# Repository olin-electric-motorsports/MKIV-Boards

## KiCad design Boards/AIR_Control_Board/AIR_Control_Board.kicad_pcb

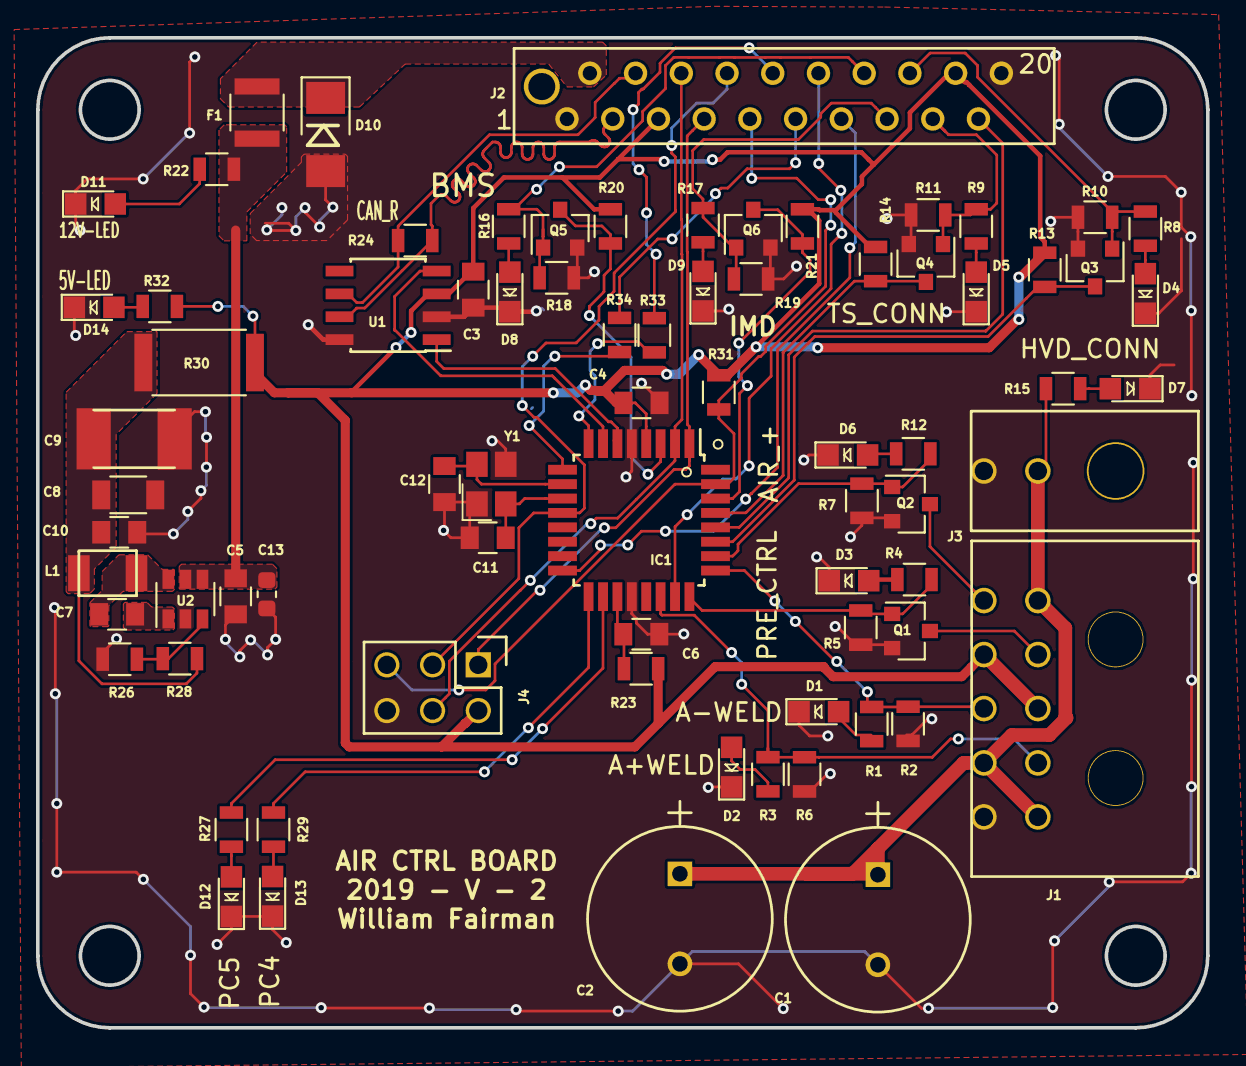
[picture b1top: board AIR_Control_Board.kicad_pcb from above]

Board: 2 copper layers, 65.0 x 55.0 mm, 76 parts (0 on the bottom side), 56 nets.

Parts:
C1, C2: CP_1mF; C_Radial_D10_L13_P5_OEM
C3, C4, C5, C7: C_0.1uF; C_0805_OEM
C6: C_100pF; C_0805_OEM
C8: C_22uF; C_1206_OEM
C9: C_33uF; C_1812_updated
C10: C_47uF; C_0805_OEM
C11, C12: C_30pF; C_0805_OEM
C13: C_2.2uF; C_0603_1608Metric
D1, D2, D3, D4, D5, D6, D7, D8, D9, D11, D12, D13, D14: LED_0805; LED_0805_OEM
D10: D_Zener_18V; DO-214AA
F1: 500mA; Fuse_1210
IC1: ATMEGA16M1; TQFP-32_7x7mm_Pitch0.8mm
J1: MicroFit_RA_10
J2: MM_F_VT_20; micromatch_female_vert_20
J3: MicroFit_RA_V_2
J4: CONN_02X03; Pin_Header_Straight_2x03
L1: L_100uH
Q1, Q2, Q3, Q4, Q5, Q6: SSM3K333R; SOT-23F
R1, R3, R4, R12, R24, R27, R29, R32, R33, R34: R_200; R_0805_OEM
R2, R5, R6, R7, R13, R14, R20, R21, R31: R_10K; R_0805_OEM
R8, R9, R15, R16, R17, R22: R_1K; R_0805_OEM
R10, R11, R18, R19, R28: R_100K; R_0805_OEM
R23: R_100; R_0805_OEM
R26: R_25K; R_0805_OEM
R30: R_0_2512; R_2512_OEM
U1: MCP2561-E_SN; SOIC-8_3.9x4.9mm_Pitch1.27mm_OEM
U2: TPS560430YF; SOT-23-6_OEM
Y1: Crystal_SMD; Crystal_SMD_FA238

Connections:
+12V: D10.1, F1.1, J2.2
/AIR+LSD: IC1.26, Q2.1, R7.1, R12.1
/AIR+_Weld_Detect: IC1.22, J1.4, R3.1, R6.1
/AIR-_Weld_Detect: IC1.25, J1.8, R1.1, R2.1
/Air+12V: C1.1, C2.1, J1.1, J1.5, J1.9, J3.1, R15.1
/Air+GND: J1.6, Q2.3
/BMS_Sense: IC1.16, J2.13
/CAN_N: J2.4, R24.2, U1.6
/CAN_P: J2.3, R24.1, U1.7
/Cooling_Pressure_Sense: IC1.28, J2.19
/IMD_Sense: IC1.23, J2.12
/MISO: IC1.1, J2.7, J4.1
/MOSI: IC1.2, J2.6, J4.4
/P_LED_1: IC1.17, R29.1
/P_LED_2: IC1.18, R27.1
/Precharge-: J1.2, Q1.3
/PrechargeCTL: IC1.24, Q1.1, R4.1, R5.1
/RESET: IC1.31, J2.9, J4.5, R31.2
/RJ45_LED1: IC1.8, R33.1
/RJ45_LED2: IC1.9, R34.1
/SCK: IC1.12, J2.8, J4.3
/SenseConnToHVD: IC1.27, Q3.3, R13.2
/SenseMainTSConn: IC1.29, Q4.3, R14.2
/ShutdownSense_BMS: J2.14, Q5.1, R16.1, R18.1
/ShutdownSense_HVD_Conn: J2.16, Q3.1, R8.1, R10.1
/ShutdownSense_IMD: J2.15, Q6.1, R17.1, R19.1
/ShutdownSense_MainPack: J2.17, Q4.1, R9.1, R11.1
/XCAN_N: IC1.7, U1.4
/XCAN_P: IC1.6, U1.1
/ss_BMS: IC1.3, Q5.3, R20.2
/ss_IMD: IC1.30, Q6.3, R21.2
GND: C1.2, C2.2, C3.2, C4.2, C5.2, C6.2, C8.2, C9.2, C10.2, C11.2, C12.2, C13.2, D1.1, D2.1, D3.1, D4.1, D5.1, D6.1, D7.1, D8.1, D9.1, D10.2, D11.1, D12.1, D13.1, D14.1, IC1.5, IC1.20, J1.10, J2.1, J2.20, J3.2, J4.6, Q1.2, Q2.2, Q3.2, Q4.2, Q5.2, Q6.2, R2.2, R5.2, R6.2, R7.2, R10.2, R11.2, R18.2, R19.2, R26.2, U1.2, U1.8, U2.2, Y1.2, Y1.4
unnamed: C6.1, IC1.19, R23.2
unnamed: C7.1, U2.1
unnamed: C7.2, L1.1, U2.6
unnamed: C8.1, C9.1, C10.1, L1.2, R28.1, R30.2
unnamed: C11.1, IC1.11, Y1.1
unnamed: C12.1, IC1.10, Y1.3
unnamed: C5.1, C13.1, F1.2, R22.1, U2.4, U2.5
unnamed: D1.2, R1.2
unnamed: D2.2, R3.2
unnamed: D3.2, R4.2
unnamed: D4.2, R8.2
unnamed: D5.2, R9.2
unnamed: D6.2, R12.2
unnamed: D7.2, R15.2
unnamed: D8.2, R16.2
unnamed: D9.2, R17.2
unnamed: D11.2, R22.2
unnamed: D12.2, R27.2
unnamed: D13.2, R29.2
unnamed: D14.2, R32.2
unnamed: J2.10, R33.2
unnamed: J2.11, R34.2
unnamed: R26.1, R28.2, U2.3
VCC: C3.1, C4.1, IC1.4, J1.3, J1.7, J2.5, J2.18, J4.2, R13.1, R14.1, R20.1, R21.1, R23.1, R30.1, R31.1, R32.1, U1.3

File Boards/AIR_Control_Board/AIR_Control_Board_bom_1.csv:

Component,Description,Part,References,Value,Footprint,Quantity Per PCB,Datasheet,Package,MPN,Purchasing Link,MFN,PurchasingLink,DK,Purchase_Link
1,,CP_1mF,C1 C2,CP_1mF,C_Radial_D10_L13_P5_OEM,2,http://nichicon-us.com/english/products/pdfs/e-uvz.pdf,"Radial, Can",493-1305-ND,https://www.digikey.com/products/en?keywords=493-1305-ND,Digi-Key,,,
2,"Capacitor, 0.1uF, 50V, 5%, 0805",C_0.1uF,C3 C4 C7 C10,C_0.1uF,C_0805_OEM,4,http://datasheets.avx.com/X7RDielectric.pdf,Value,478-3352-1-ND,,Digi-Key,https://www.digikey.com/products/en?keywords=478-3352-1-ND,,
3,"Capacitor, 100pF, 50V, 5%, 0805",C_100pF,C6,C_100pF,C_0805_OEM,1,https://content.kemet.com/datasheets/KEM_C1003_C0G_SMD.pdf,Value,399-1122-1-ND,,Digi-Key,https://www.digikey.com/product-detail/en/kemet/C0805C101J5G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,,
4,CAP CER 1UF 25V X7R 0805,C_1uF,C9,C_1uF,C_0805_OEM,1,http://datasheets.avx.com/X7RDielectric.pdf,Value,478-10487-1-ND,,Digi-Key,https://www.digikey.com/product-detail/en/avx-corporation/08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,,
5,"Capacitor, 22uF, 16V, 20%, 1206",C_22uF,C5,C_22uF,C_1206_OEM,1,http://www.samsungsem.com/kr/support/product-search/mlcc/__i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,Value,1276-2725-1-ND,,Digi-Key,https://www.digikey.com/products/en?keywords=1276-2725-1-ND,,
6,"Capacitor, 30pF, 50V, 5%, 0805",C_30pF,C11 C12,C_30pF,C_0805_OEM,2,https://media.digikey.com/pdf/Data%20Sheets/Samsung%20PDFs/C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,Value,1276-1130-1-ND,,Digi-Key,https://www.digikey.com/product-detail/en/samsung-electro-me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,,
7,"Capacitor, 47uF, 6.3V, 20%, 0805",C_47uF,C8,C_47uF,C_0805_OEM,1,http://www.yuden.co.jp/productdata/catalog/en/mlcc_all_e.pdf,Value,587-4280-1-ND,,Digi-Key,https://www.digikey.com/product-detail/en/taiyo-yuden/JMK212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,,
8,"Diode, Zener, 18V, 5W, 5%",D_Zener_18V,D10,D_Zener_18V,DO-214AA,1,http://www.mccsemi.com/up_pdf/SMBJ5338B-SMBJ5388B(SMB).pdf,DO-214AA (SMB),SMBJ5355B-TPMSCT-ND,,Digi-Key,https://www.digikey.com/products/en?keywords=SMBJ5355B-TPMSCT-ND,,
9,"LED, Green, 2.2V, 20mA, 0805",LED_0805,D1 D2 D3 D4 D5 D6 D7 D8 D9 D11 D12 D13 D14,LED_0805,LED_0805_OEM,13,http://www.osram-os.com/Graphics/XPic9/00078860_0.pdf,Value,475-1410-1-ND,,DK Digi-Key,https://www.digikey.com/products/en?keywords=475-1410-1-ND,,
10,"Fuse, PTC, 500mA, 16V, 1210",F_500mA_16V,F1,500mA,Fuse_1210,1,https://belfuse.com/resources/CircuitProtection/datasheets/0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,Value,507-1786-1-ND,,Digi-Key,https://www.digikey.com/product-detail/en/bel-fuse-inc/0ZCH0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,,
11,"Microcontroller, 8-bit, 1KB RAM, 16KB Flash",ATMEGA16M1,IC1,ATMEGA16M1,TQFP-32_7x7mm_Pitch0.8mm,1,http://www.atmel.com/Images/Atmel-8209-8-bit%20AVR%20ATmega1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,Value,ATMEGA16M1-AU-ND,,Digi-Key,https://www.digikey.com/product-detail/en/atmel/ATMEGA16M1-A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,,
12,"Connector header through hole 2x3 0.100"" (2.54mm)",CONN_02X03,J4,CONN_02X03,Pin_Header_Straight_2x03,1,http://portal.fciconnect.com/Comergent//fci/drawing/67996.pdf,Value,609-3234-ND,,Digi-Key,https://www.digikey.com/product-detail/en/amphenol-fci/67997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,,
13,Micro-MaTch connector 20 pin female vertical,MM_F_VT_20,J2,MM_F_VT_20,micromatch_female_vert_20,1,http://www.te.com/commerce/DocumentDelivery/DDEController?Ac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,,2-338068-0,,TE,http://www.te.com/global-en/product-2-338068-0.html,,
14,,MicroFit_RA_10,J1,MicroFit_RA_10,MicroFit_RA_10,1,https://www.molex.com/pdm_docs/sd/430451000_sd.pdf,,WM1817-ND,,DK,https://www.digikey.com/product-detail/en/molex/0430451000/W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,,
15,,MicroFit_RA_V_2,J3,MicroFit_RA_V_2,MicroFit_RA_V_2,1,https://www.molex.com/pdm_docs/sd/430450200_sd.pdf,,WM1865-ND,https://www.digikey.com/product-detail/en/molex/0430450200/W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,,,MFN,
16,"Inductor, 4.7uH, 4.4A, 25mOhm, 20%",L_4.7uH,L1,L_4.7uH,4.7uH_Inductor_OEM,1,https://product.tdk.com/info/en/documents/wdcatalog/withdraw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,Value,445-6583-1-ND,,Digi-Key,https://www.digikey.com/product-detail/en/tdk-corporation/VL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,,
17,"MOSFET, N-channel, 30V, 6A",SSM3K333R,Q1 Q2 Q3 Q4 Q5 Q6,SSM3K333R,SOT-23F,6,https://drive.google.com/drive/folders/0B-V-iZf33Y4GNzhDQTJZanJRbVk,SOT-23-3 Flat Leads,SSM3K333RLFCT-ND,,Digi-Key,https://www.digikey.com/product-detail/en/toshiba-semiconduc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,,https://www.digikey.com/product-detail/en/toshiba-semiconduc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
18,"Resistor, 0 ohm jumper, 3W, 2512",R_0_2512,R30,R_0_2512,R_2512_OEM,1,http://www.te.com/commerce/DocumentDelivery/DDEController?Ac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,,A121322CT-ND,,DK,https://www.digikey.com/products/en?keywords=A121322CT-ND,,
19,"Resistor, 100, 0.25W, 1%, 0805",R_100,R23,R_100,R_0805_OEM,1,https://www.seielect.com/Catalog/SEI-rncp.pdf,Value,RNCP0805FTD100RCT-ND,,Digi-Key,https://www.digikey.com/products/en?keywords=RNCP0805FTD100RCT-ND,,
20,"Resistor, 100K, 0.125W, 1%, 0805",R_100K,R10 R11 R18 R19,R_100K,R_0805_OEM,4,https://industrial.panasonic.com/cdbs/www-data/pdf/RDA0000/A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,,P100KCCT-ND,,DK,https://www.digikey.com/product-detail/en/panasonic-electron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,,
21,"Resistor, 10K, 0.25W, 1%, 0805",R_10K,R2 R5 R6 R13 R14 R20 R21 R25 R26 R31,R_10K,R_0805_OEM,10,http://www.bourns.com/data/global/pdfs/CRS.pdf,,CRS0805-FX-1002ELFCT-ND,,DK,https://www.digikey.com/products/en?keywords=CRS0805-FX-1002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,,
22,"Resistor, 100K, 0.125W, 1%, 0805",R_100K,R7,R_10K,R_0805_OEM,1,https://industrial.panasonic.com/cdbs/www-data/pdf/RDA0000/A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,,P100KCCT-ND,,DK,https://www.digikey.com/product-detail/en/panasonic-electron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,,
23,"Resistor, 1K, 0.25W, 1%, 0805",R_1K,R8 R9 R15 R16 R17 R22,R_1K,R_0805_OEM,6,https://www.seielect.com/Catalog/SEI-rncp.pdf,,RNCP0805FTD1K00CT-ND,,DK,https://www.digikey.com/products/en?keywords=RNCP0805FTD1K00CT-ND,,
24,"Resistor, 200, 0.125W, 5%, 0805",R_200,R1 R3 R4 R24 R27 R29 R32 R33 R34,R_200,R_0805_OEM,9,https://www.seielect.com/Catalog/SEI-RMCF_RMCP.pdf,Value,RMCF0805JT200RCT-ND,,DK Digi-Key,https://www.digikey.com/products/en?keywords=RMCF0805JT200RCT-ND,,
25,"Resistor, 1K, 0.25W, 1%, 0805",R_1K,R12,R_200,R_0805_OEM,1,https://www.seielect.com/Catalog/SEI-rncp.pdf,,RNCP0805FTD1K00CT-ND,,DK,https://www.digikey.com/products/en?keywords=RNCP0805FTD1K00CT-ND,,
26,"Resistor, 51.1K, 0.125W, 1%, 0805",R_51.1K,R28,R_51.1K,R_0805_OEM,1,https://industrial.panasonic.com/cdbs/www-data/pdf/RDA0000/A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,,P51.1KCCT-ND,,DK,https://www.digikey.com/product-detail/en/panasonic-electron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,,
27,"High speed CAN transceiver, 1Mb/s",MCP2561-E_SN,U1,MCP2561-E_SN,SOIC-8_3.9x4.9mm_Pitch1.27mm_OEM,1,http://www.microchip.com/mymicrochip/filehandler.aspx?ddocna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,,MCP2561-E/SN-ND,,DK,https://www.digikey.com/products/en?keywords=mcp2561-e%2Fsn,,
28,"Buck converter, 4.5-17V input, adj 0.76-7V output, 1A, 580kHz",TPS561201,U2,TPS561201,SOT-23-6_OEM,1,http://www.ti.com/lit/ds/symlink/tps561201.pdf,Value,TPS561201,,Digi-Key,https://www.digikey.com/products/en?keywords=296-46928-1-ND,,
29,CRYSTAL 16.0000MHZ 18PF SMD,Crystal_SMD,Y1,Crystal_SMD,Crystal_SMD_FA238,1,https://support.epson.biz/td/api/doc_check.php?dl=brief_FA-2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,Value,SER3686CT-ND,,Digi-Key,https://www.digikey.com/products/en?keywords=SER3686CT-ND,,





Component Groups:,29
Component Count:,76
Fitted Components:,76
Number of PCBs:,1
Total components:,76
Schematic Version:,1
Schematic Date:,2018-11-01
BoM Date:,Sun 10 Feb 2019 09:32:41 AM EST
Schematic Source:,/home/william/Desktop/MKIV-Boards/Boards/AIR_Control_Board/AIR_Control_Board.sch
KiCad Version:,Eeschema 5.0.0-fee4fd1~66~ubuntu16.04.1

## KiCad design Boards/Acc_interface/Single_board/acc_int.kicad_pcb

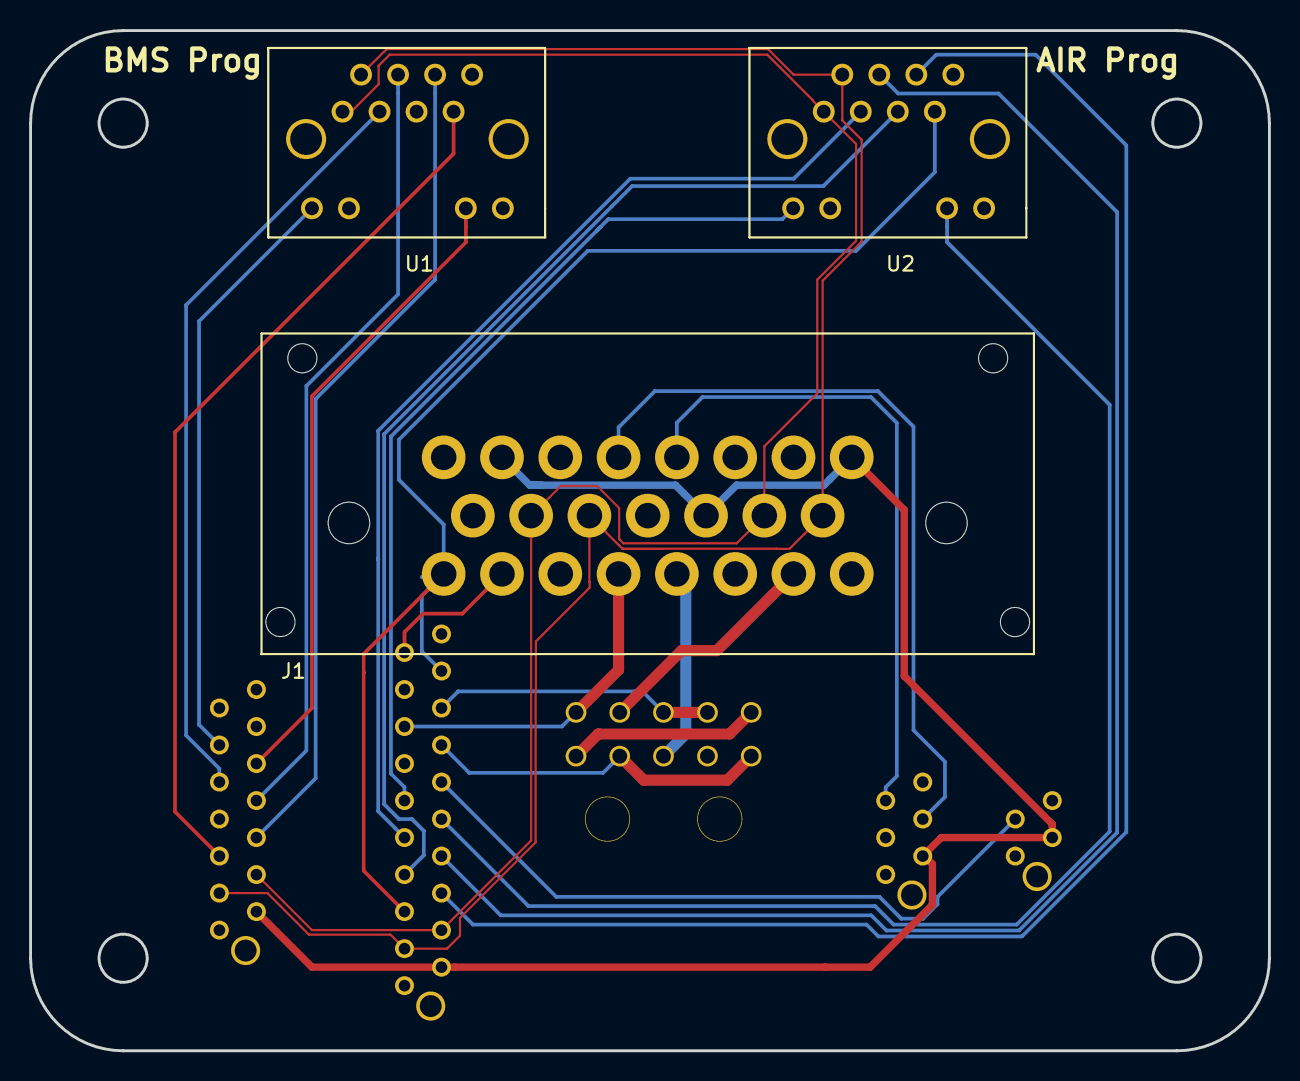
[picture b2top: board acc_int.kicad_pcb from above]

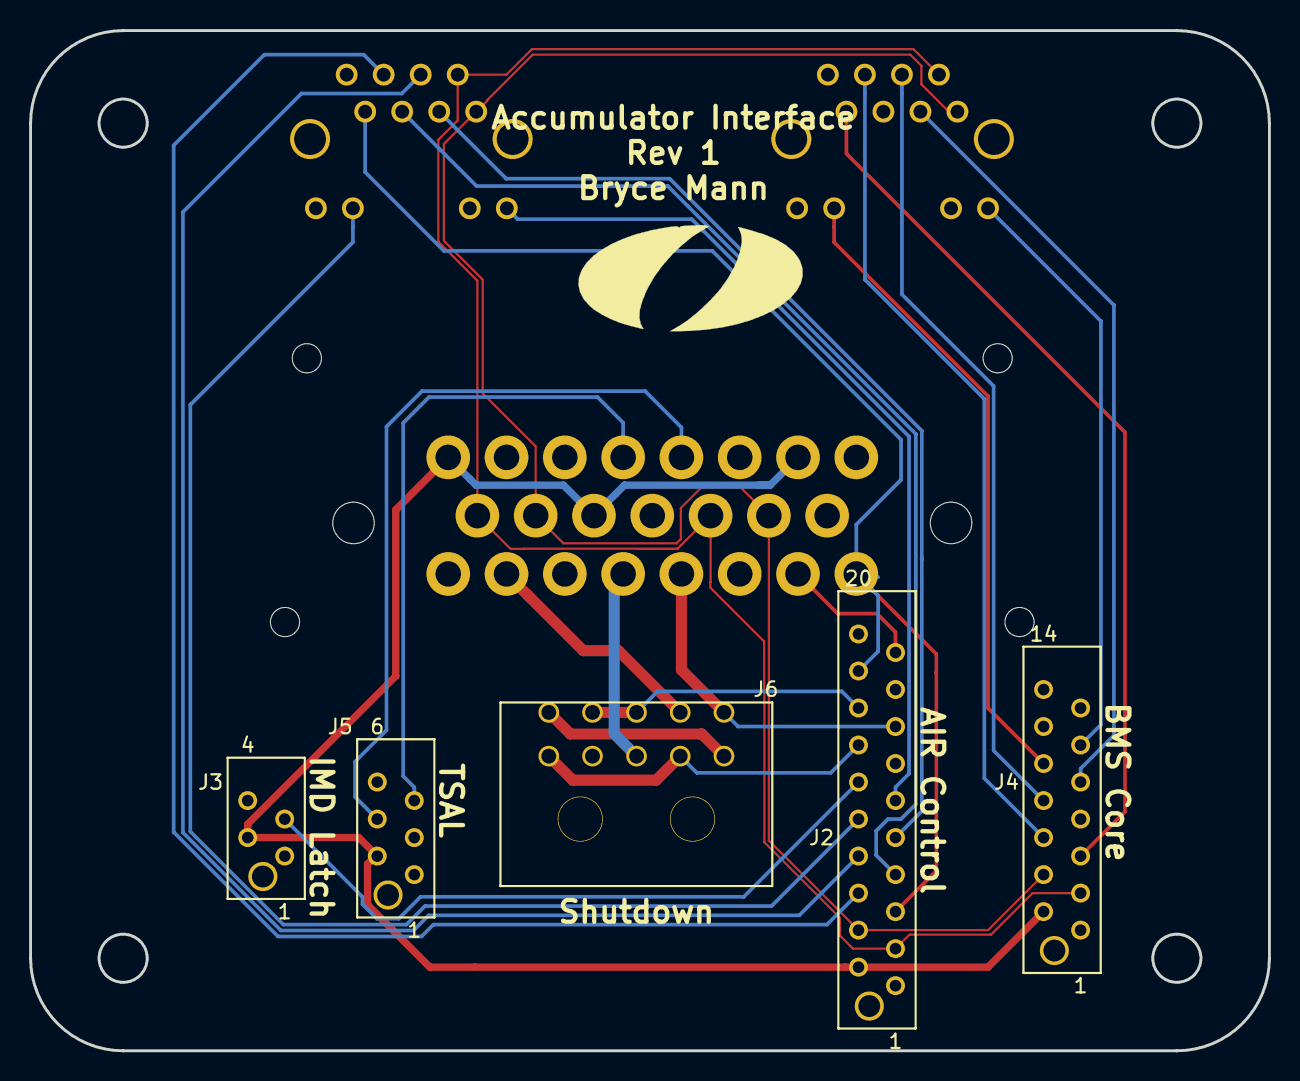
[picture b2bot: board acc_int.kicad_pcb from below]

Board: 4 copper layers, 85.0 x 70.0 mm, 8 parts (5 on the bottom side), 33 nets.

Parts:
J1: Ampseal_23_VT; Ampseal_23
J2: MM_F_RA_20; micromatch_female_vert_20
J3: MM_F_RA_04; micromatch_female_vert_4
J4: MM_F_RA_14; micromatch_female_vert_14
J5: MM_F_RA_06; micromatch_female_vert_6
J6: MicroFit_RA_10
U1, U2: RJ45_VT; RJ45-Vertical

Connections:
/5V_AIR: J1.16, J2.5, J2.18, U2.7
/5V_BMS: J4.5, U1.7
/12V: J1.2, J1.8, J1.13, J2.2, J3.2, J4.2, J5.2
/BMS_SENSE: J2.13, J4.13
/BSPD_Current_sense: J1.23, J4.14
/CAN_HIGH: J1.11, J1.15, J2.3, J4.3, U1.2, U2.2
/CAN_LOW: J1.10, J1.14, J2.4, J4.4, U1.1, U2.1
/Cooling_pressure_sense: J1.17, J2.19
/FAN_PWM: J1.21, J4.12
/IMD_SENSE: J2.12, J3.3
/LED1_AIR: J2.10, U2.10
/LED1_BMS: J4.10, U1.10
/LED2_AIR: J2.11, U2.12
/LED2_BMS: J4.11, U1.12
/MISO_AIR: J2.7, U2.5
/MISO_BMS: J4.7, U1.5
/MOSI_AIR: J2.6, U2.6
/MOSI_BMS: J4.6, U1.6
/RESET_AIR: J2.9, U2.3
/RESET_BMS: J4.9, U1.3
/SCK_AIR: J2.8, U2.4
/SCK_BMS: J4.8, U1.4
/Shutdown_BMS: J2.14, J6.2, J6.5
/Shutdown_E-STOP: J1.22, J6.7
/Shutdown_Final: J1.20, J6.3
/Shutdown_HVD: J2.16, J6.8, J6.9
/Shutdown_IMD: J1.19, J2.15, J6.6
/Shutdown_MP: J2.17, J6.1, J6.10
/TSAL+_G: J1.5, J5.5
/TSAL+_R: J1.3, J5.3
/TSAL-_G: J1.6, J5.6
/TSAL-_R: J1.4, J5.4
GND: J1.1, J1.7, J1.9, J1.12, J1.18, J2.1, J2.20, J3.1, J3.4, J4.1, J5.1, J6.4, U1.8, U1.9, U1.11, U1.13, U1.14, U2.8, U2.9, U2.11, U2.13, U2.14

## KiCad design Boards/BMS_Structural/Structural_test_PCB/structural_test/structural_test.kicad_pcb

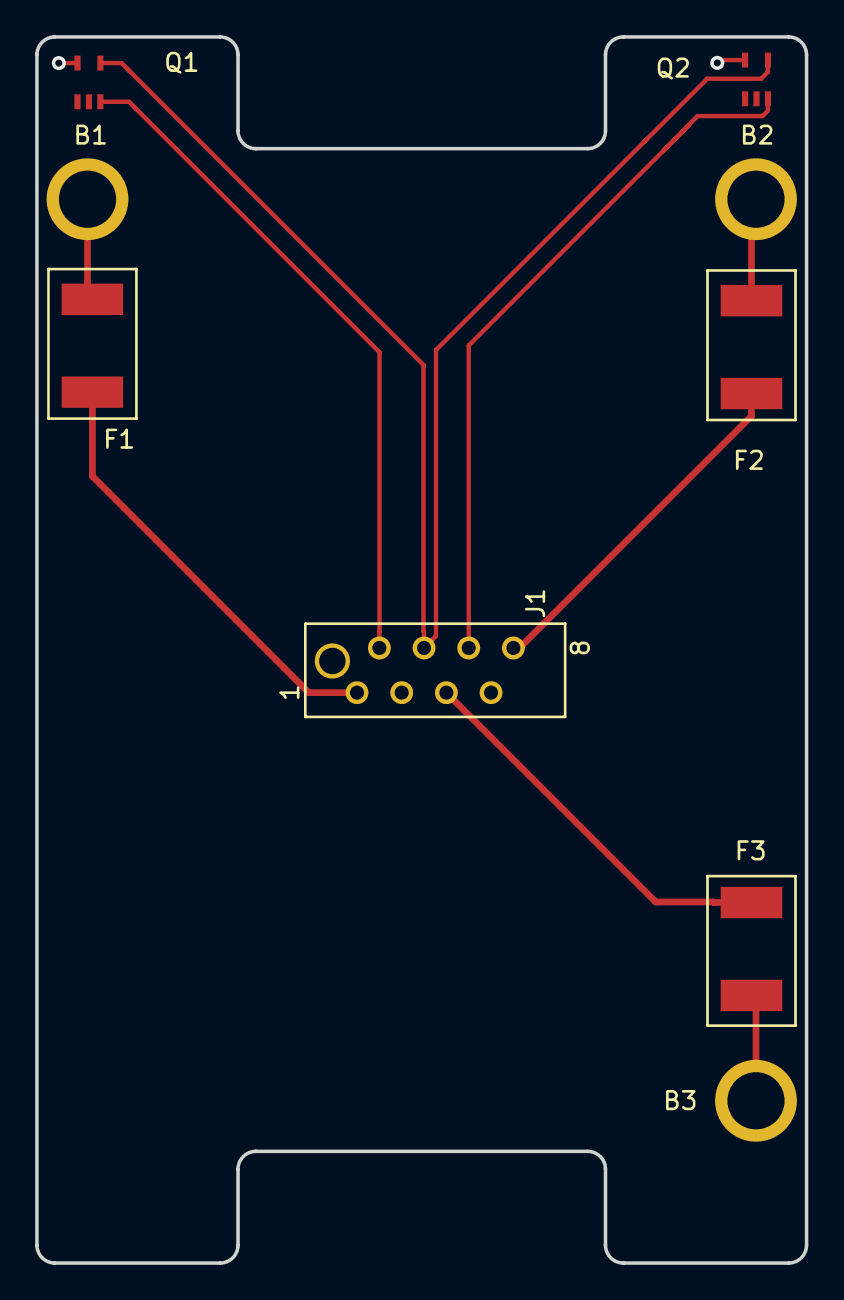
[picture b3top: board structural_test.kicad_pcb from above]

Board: 2 copper layers, 43.8 x 69.7 mm, 9 parts (0 on the bottom side), 10 nets.

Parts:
B1, B2, B3: Bolt_connect_4-40; Bolt_connect_4-40_round
F1, F2, F3: 200mA_Fuse; Fuse_1812
J1: MM_F_VT_08; micromatch_female_vert_8
Q1, Q2: LMT85-Q1

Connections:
/5V: J1.4, Q1.5, Q2.5
/gnd: J1.7, Q1.1, Q2.1
/temp1: J1.2, Q1.4
/temp2: J1.6, Q2.4
/v+: F3.1, J1.5
/v-: F2.1, J1.8
/volt: F1.1, J1.1
unnamed: B1.1, F1.2
unnamed: B2.1, F2.2
unnamed: B3.1, F3.2

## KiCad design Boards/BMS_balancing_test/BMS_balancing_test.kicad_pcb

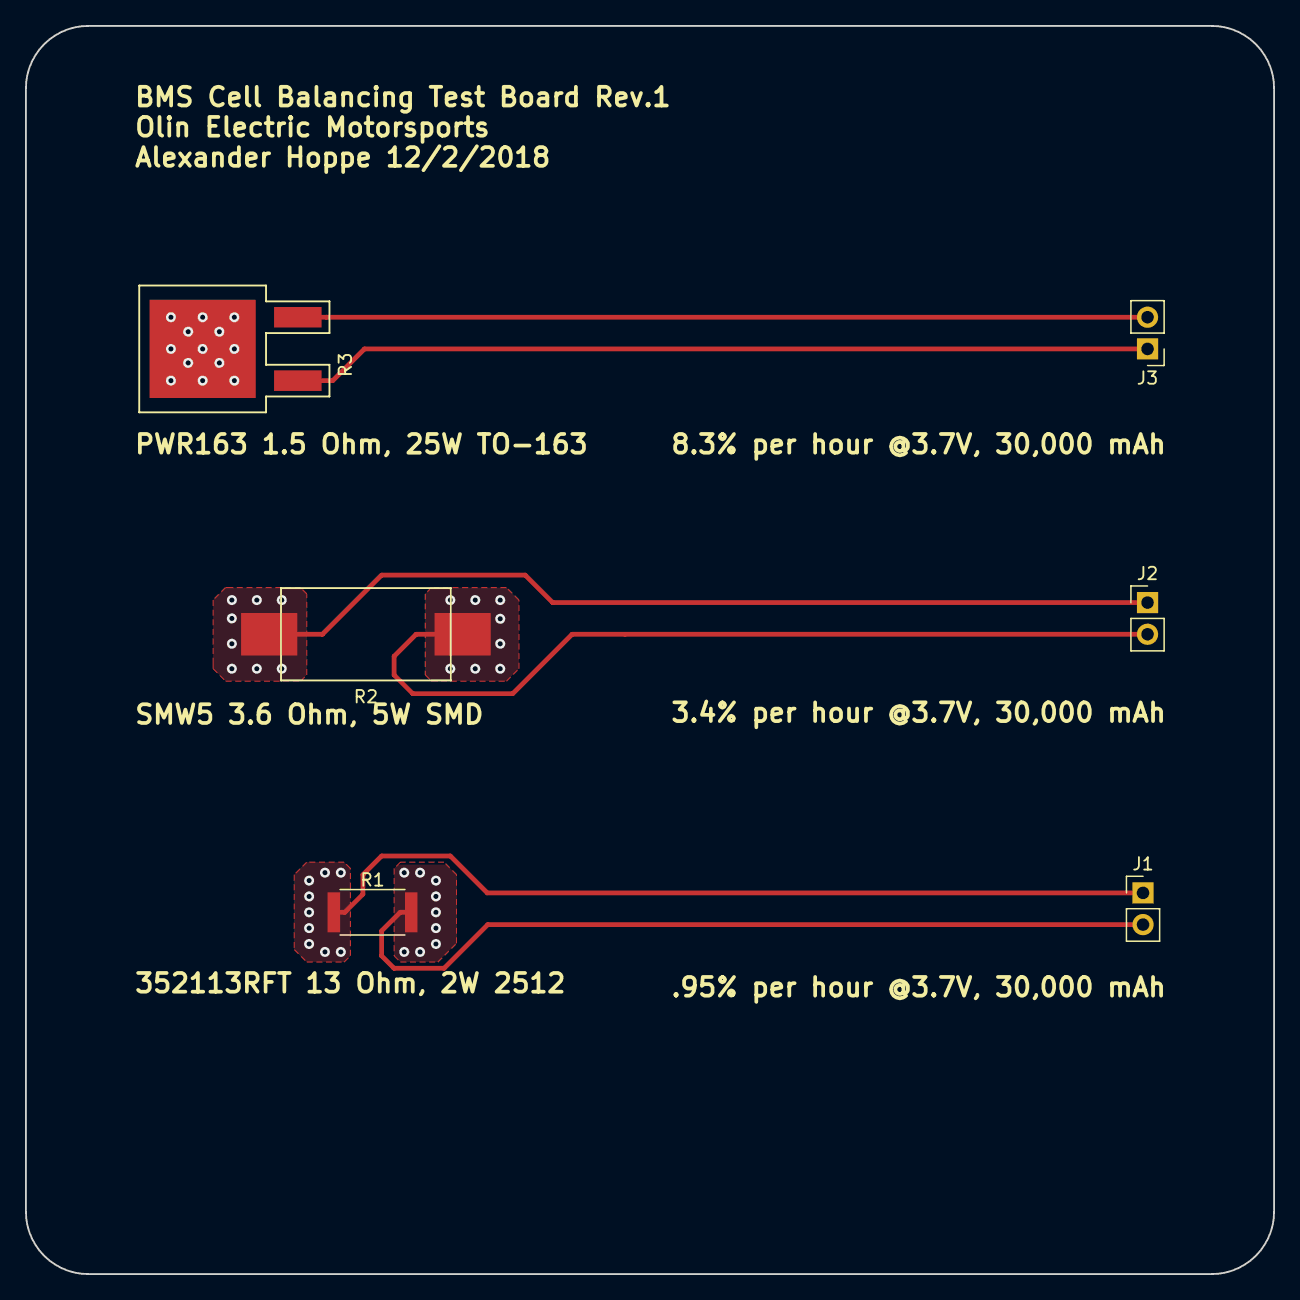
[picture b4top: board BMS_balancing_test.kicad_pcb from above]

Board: 2 copper layers, 100.0 x 100.0 mm, 6 parts (0 on the bottom side), 6 nets.

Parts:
J1, J2, J3: CONN_01x02; PinHeader_1x02_P2.54mm_Vertical
R1: R_13_2W_2512_0; R_2512_OEM
R2: R_3.6_5W_SMD; SM_5
R3: R_1.3_25W_TO163; PWR163

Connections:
unnamed: J1.1, R1.1
unnamed: J1.2, R1.2
unnamed: J2.1, R2.1
unnamed: J2.2, R2.2
unnamed: J3.1, R3.1
unnamed: J3.2, R3.2

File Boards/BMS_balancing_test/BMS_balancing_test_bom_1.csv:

Component,Description,Part,References,Value,Footprint,Quantity Per PCB,Datasheet,MPN,MFN,MFG,PurchasingLink
1,CONN HEADER 2 POS 2.54mm,CONN_01x02,J1 J2 J3,CONN_01x02,PinHeader_1x02_P2.54mm_Vertical,3,https://katalog.we-online.de/em/datasheet/6130xx11121.pdf,732-5315-ND,DK,,
2,RES SMD 1.5 OHM 1% 25W DPAK,R_1.3_25W_TO163,R3,R_1.3_25W_TO163,PWR163,1,https://www.bourns.com/docs/Product-Datasheets/PWR163.pdf,PWR163S-25-1R50F-ND,DK,,
3,"Resistor, 13 ohm 1%, 2W, 2512",R_13_2W_2512_0,R1,R_13_2W_2512_0,R_2512_OEM,1,https://www.te.com/commerce/DocumentDelivery/DDEController?A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,A115987CT-ND,,DK,https://www.digikey.com/product-detail/en/te-connectivity-pa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
4,"Resistor, 13 ohm 1%, 2W, 2512",R_3.6_5W_SMD,R2,R_3.6_5W_SMD,SM_5,1,https://www.te.com/commerce/DocumentDelivery/DDEController?A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,A131834CT-ND,,DK,https://www.digikey.com/product-detail/en/te-connectivity-pa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





Component Groups:,4
Component Count:,6
Fitted Components:,6
Number of PCBs:,1
Total components:,6
Schematic Version:,1
Schematic Date:,2018-12-02
BoM Date:,Sat 15 Dec 2018 01:55:22 PM EST
Schematic Source:,/home/aehoppe/Documents/Formula/MKIV-Boards/Boards/BMS_balancing_test/BMS_balancing_test.sch
KiCad Version:,Eeschema 5.0.2-bee76a0~70~ubuntu16.04.1

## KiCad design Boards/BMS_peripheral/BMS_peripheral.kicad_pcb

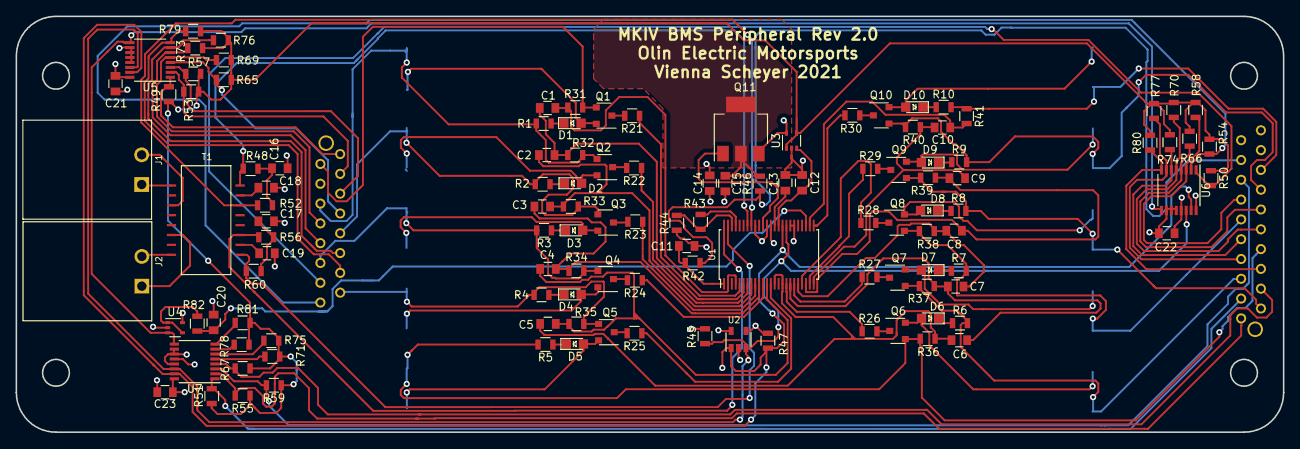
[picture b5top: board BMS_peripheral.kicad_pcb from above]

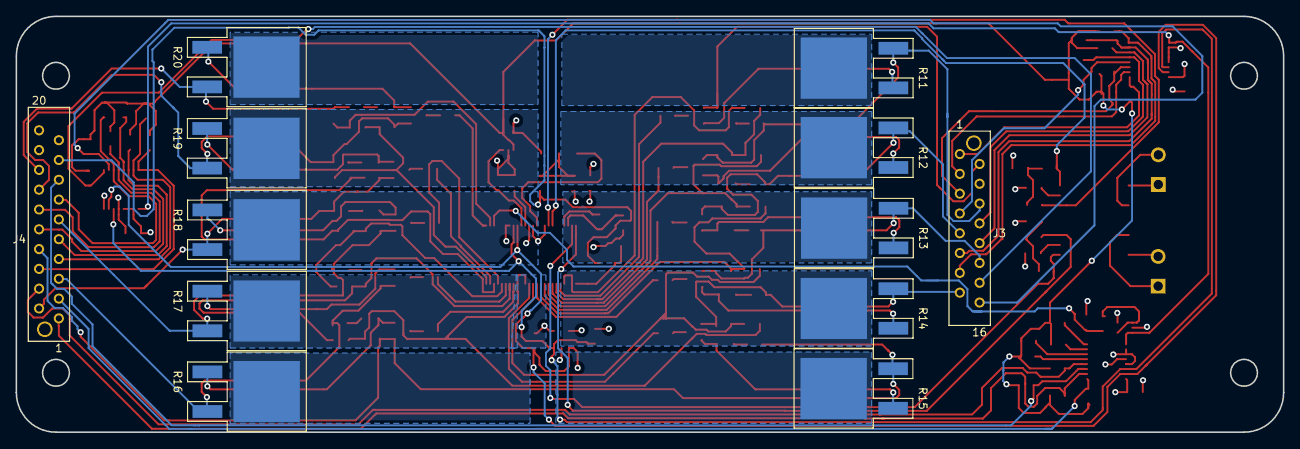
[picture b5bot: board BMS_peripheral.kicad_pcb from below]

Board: 4 copper layers, 162.6 x 53.3 mm, 132 parts (12 on the bottom side), 114 nets.

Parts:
C1, C2, C3, C4, C5, C6, C7, C8, C9, C10, C16, C17, C18, C19, C20: C_10nF; C_0805_OEM
C11, C15: C_0.1uF; C_0805_OEM
C12, C13, C14: 1uF; C_0805_OEM
C21, C22, C23: C_1uF; C_0805_OEM
D1, D2, D3, D4, D5, D6, D7, D8, D9, D10: LED_0805; LED_0805_OEM
J1, J2: isoSPI-Cutout; iso_spi_cutout
J3: MM_F_VT_16; micromatch_female_vert_16
J4: MM_F_VT_20; micromatch_female_vert_20
Q1, Q2, Q3, Q4, Q5, Q6, Q7, Q8, Q9, Q10: BSS308PE; SOT-23-3_OEM
Q11: NSS1C201MZ4; SOT-223
R1, R2, R3, R4, R5, R6, R7, R8, R9, R10: R_475; R_0805_OEM
R11, R12, R13, R14, R15, R16, R17, R18, R19, R20: R_3.3_25W_TO163; PWR163
R21, R22, R23, R24, R25, R26, R27, R28, R29, R30, R45, R47: R_4.99K; R_0805_OEM
R31, R32, R33, R34, R35, R36, R37, R38, R39, R40, R41, R42, R46, R82: R_100; R_0805_OEM
R43, R44: R_1K; R_0805_OEM
R48, R52, R56, R60: R_60.4; R_0805_OEM
R49, R50, R51, R53, R54, R55, R57, R58, R59, R65, R66, R67, R69, R70, R71, R73, R74, R75, R76, R77, R78, R79, R80, R81: R_100K; R_0805_OEM
T1: T_LAN_7490100111A
U1: LTC6811-1; TSSOP-48_LTC6811-1
U2: 24AA01; SOT-23-5_OEM_24AA01
U3, U4: MCP6001T-I-LT; SOT-353_SC-70-5
U5, U6, U7: LTC1380IGN; SSOP-16_3.9x4.9mm_P0.635mm

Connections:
/CELL0_VOLT: J3.2, Q1.2, R31.1
/CELL1_VOLT: J3.6, Q2.2, R1.2, R11.2, R32.1
/CELL2_VOLT: J3.9, Q3.2, R2.2, R12.2, R33.1
/CELL3_VOLT: J3.12, Q4.2, R3.2, R13.2, R34.1
/CELL4_VOLT: J3.15, Q5.2, R4.2, R14.2, R35.1
/CELL5_VOLT: J4.8, Q6.2, R5.2, R15.2, R36.1
/CELL6_VOLT: J4.5, Q7.2, R6.2, R16.2, R37.1
/CELL7_VOLT: J4.11, Q8.2, R7.2, R17.2, R38.1
/CELL8_VOLT: J4.2, Q9.2, R8.2, R18.2, R39.1
/CELL9_VOLT: J4.14, Q10.2, R9.2, R19.2, R40.1
/CELL10_VOLT: J4.16, R10.2, R20.2, R41.1
/IMA: R52.2, T1.14, U1.41
/IMB: R60.2, T1.9, U1.47
/IPA: R48.1, T1.16, U1.42
/IPB: R56.1, T1.11, U1.48
/MODULE1_TEMP1: J3.1, R49.2, U5.1
/MODULE1_TEMP2: J3.3, R53.2, U5.2
/MODULE2_TEMP1: J3.5, R57.2, U5.3
/MODULE2_TEMP2: J3.7, R65.2, U5.4
/MODULE3_TEMP1: J3.8, R69.2, U5.5
/MODULE3_TEMP2: J3.10, R73.2, U5.6
/MODULE4_TEMP1: J3.11, R76.2, U5.7
/MODULE4_TEMP2: J3.13, R79.2, U5.8
/MODULE5_TEMP1: J3.14, R50.2, U6.1
/MODULE5_TEMP2: J3.16, R54.2, U6.2
/MODULE6_TEMP1: J4.13, R58.2, U6.3
/MODULE6_TEMP2: J4.12, R66.2, U6.4
/MODULE7_TEMP1: J4.10, R70.2, U6.5
/MODULE7_TEMP2: J4.9, R74.2, U6.6
/MODULE8_TEMP1: J4.7, R77.2, U6.7
/MODULE8_TEMP2: J4.6, R80.2, U6.8
/MODULE9_TEMP1: J4.3, R51.2, U7.1
/MODULE9_TEMP2: J4.1, R55.2, U7.2
/MODULE10_TEMP1: J4.15, R59.2, U7.3
/MODULE10_TEMP2: J4.4, R67.2, U7.4
/SCL: R47.2, U1.33, U2.1, U5.15, U6.15, U7.15
/SDA: R45.2, U1.32, U2.3, U5.14, U6.14, U7.14
/TEMP_SENSE: C20.1, R82.1, U1.27
/V+: J4.17, R42.1, R46.1
/VREF2: R49.1, R50.1, R51.1, R53.1, R54.1, R55.1, R57.1, R58.1, R59.1, R65.1, R66.1, R67.1, R69.1, R70.1, R71.1, R73.1, R74.1, R75.1, R76.1, R77.1, R78.1, R79.1, R80.1, R81.1, U3.1, U3.4
/VREG: C14.1, C21.1, C22.1, C23.1, J4.18, Q11.3, R45.1, R47.1, U1.37, U1.40, U2.4, U3.5, U4.5, U5.16, U6.13, U6.16, U7.12, U7.16
/~DIS~1: R30.1, U1.25
/~DIS~2: R29.1, U1.23
/~DIS~3: R28.1, U1.21
/~DIS~4: R27.1, U1.19
/~DIS~5: R26.1, U1.17
/~DIS~6: R25.1, U1.13
/~DIS~7: R24.1, U1.11
/~DIS~8: R23.1, U1.9
/~DIS~9: R22.1, U1.7
/~DIS~10: R21.1, U1.5
GND: C11.2, C12.2, C13.2, C14.2, C15.2, C16.2, C17.2, C18.2, C19.2, C20.2, C21.2, C22.2, C23.2, J3.4, J4.19, R44.2, U1.30, U1.31, U1.36, U2.2, U2.5, U3.2, U4.2, U5.10, U5.11, U5.12, U5.13, U6.10, U6.11, U6.12, U7.10, U7.11, U7.13
unnamed: C1.1, R31.2, U1.2, U1.4
unnamed: C1.2, C2.1, R32.2, U1.6
unnamed: C2.2, C3.1, R33.2, U1.8
unnamed: C3.2, C4.1, R34.2, U1.10
unnamed: C4.2, C5.1, R35.2, U1.12
unnamed: C5.2, C6.1, R36.2, U1.14, U1.16
unnamed: C6.2, C7.1, R37.2, U1.18
unnamed: C7.2, C8.1, R38.2, U1.20
unnamed: C8.2, C9.1, R39.2, U1.22
unnamed: C9.2, C10.1, R40.2, U1.24
unnamed: C10.2, R41.2, U1.26
unnamed: C11.1, R42.2, U1.1
unnamed: C12.1, U1.34, U3.3
unnamed: C13.1, U1.35
unnamed: C15.1, Q11.2, Q11.4, R46.2
unnamed: C16.1, R48.2, R52.1
unnamed: C17.1, R56.2, R60.1
unnamed: C18.1, T1.15
unnamed: C19.1, T1.10
unnamed: D1.1, R1.1
unnamed: D1.2, Q1.3, R11.1
unnamed: D2.1, R2.1
unnamed: D2.2, Q2.3, R12.1
unnamed: D3.1, R3.1
unnamed: D3.2, Q3.3, R13.1
unnamed: D4.1, R4.1
unnamed: D4.2, Q4.3, R14.1
unnamed: D5.1, R5.1
unnamed: D5.2, Q5.3, R15.1
unnamed: D6.1, R6.1
unnamed: D6.2, Q6.3, R16.1
unnamed: D7.1, R7.1
unnamed: D7.2, Q7.3, R17.1
unnamed: D8.1, R8.1
unnamed: D8.2, Q8.3, R18.1
unnamed: D9.1, R9.1
unnamed: D9.2, Q9.3, R19.1
unnamed: D10.1, R10.1
unnamed: D10.2, Q10.3, R20.1
unnamed: J1.1, T1.1
unnamed: J1.2, T1.3
unnamed: J2.1, T1.6
unnamed: J2.2, T1.8
unnamed: Q1.1, R21.2
unnamed: Q2.1, R22.2
unnamed: Q3.1, R23.2
unnamed: Q4.1, R24.2
unnamed: Q5.1, R25.2
unnamed: Q6.1, R26.2
unnamed: Q7.1, R27.2
unnamed: Q8.1, R28.2
unnamed: Q9.1, R29.2
unnamed: Q10.1, R30.2
unnamed: Q11.1, U1.38
unnamed: R43.1, R44.1, U1.46
unnamed: R43.2, U1.45
unnamed: R71.2, U7.5
unnamed: R75.2, U7.6
unnamed: R78.2, U7.7
unnamed: R81.2, U7.8
unnamed: R82.2, U4.1, U4.4
unnamed: U4.3, U5.9, U6.9, U7.9

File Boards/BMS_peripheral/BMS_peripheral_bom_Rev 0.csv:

Component,Description,Part,References,Value,Footprint,Quantity Per PCB,Datasheet,MPN,MFN,PurchasingLink
1,"Capacitor, 1uF, 25V, 10%, 0805",C_1uF,C12 C13 C14,1uF,C_0805_OEM,3,http://www.samsungsem.com/kr/support/product-search/mlcc/__i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,1276-2887-1-ND,DK,https://www.digikey.com/product-detail/en/samsung-electro-me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
2,"Capacitor, 0.1uF, 50V, 5%, 0805",C_0.1uF,C11 C15,C_0.1uF,C_0805_OEM,2,http://datasheets.avx.com/X7RDielectric.pdf,478-3352-1-ND,DK,https://www.digikey.com/products/en?keywords=478-3352-1-ND
3,"Capacitor, 10nF 50V X7R 0805",C_10nF,C1 C2 C3 C4 C5 C6 C7 C8 C9 C10 C16 C17 C18 C19 C20,C_10nF,C_0805_OEM,15,http://www.samsungsem.com/kr/support/product-search/mlcc/__i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,1276-1015-1-ND,DK,https://www.digikey.com/product-detail/en/samsung-electro-me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
4,"Capacitor, 1uF, 25V, 10%, 0805",C_1uF,C21 C22 C23,C_1uF,C_0805_OEM,3,http://www.samsungsem.com/kr/support/product-search/mlcc/__i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,1276-2887-1-ND,DK,https://www.digikey.com/product-detail/en/samsung-electro-me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
5,"LED, Green, 2.2V, 20mA, 0805",LED_0805,D1 D2 D3 D4 D5 D6 D7 D8 D9 D10,LED_0805,LED_0805_OEM,10,http://www.osram-os.com/Graphics/XPic9/00078860_0.pdf,475-1410-1-ND,DK,https://www.digikey.com/products/en?keywords=475-1410-1-ND
6,Micro-MaTch connector 16 pin female vertical,MM_F_VT_16,J3,MM_F_VT_16,micromatch_female_vert_16,1,http://www.te.com/commerce/DocumentDelivery/DDEController?Ac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,1-338068-6,TE,http://www.te.com/global-en/product-1-338068-6.html
7,Micro-MaTch connector 20 pin female vertical,MM_F_VT_20,J4,MM_F_VT_20,micromatch_female_vert_20,1,http://www.te.com/commerce/DocumentDelivery/DDEController?Ac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,2-338068-0,TE,http://www.te.com/global-en/product-2-338068-0.html
8,Mechanical Cutout for Zip-tie attachement,isoSPI-Cutout,J1 J2,isoSPI-Cutout,iso_spi_cutout,2,https://docs.olinelectricmotorsports.com/display/ETD/BMS#BMS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,,,
9,"MOSFET, P-channel, 30V, 2A",BSS308PE,Q1 Q2 Q3 Q4 Q5 Q6 Q7 Q8 Q9 Q10,BSS308PE,SOT-23-3_OEM,10,https://www.infineon.com/dgdl/BSS308PE_Rev2.03.pdf?folderId=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,BSS308PEH6327XTSA1CT-ND,DK,https://www.digikey.com/products/en/discrete-semiconductor-p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
10,"100V, 2.0A, Low VCE NPN Transistor",NSS1C201MZ4,Q11,NSS1C201MZ4,SOT-223,1,http://www.onsemi.com/pub/Collateral/NSS1C201MZ4-D.PDF,NSS1C201MZ4T3GOSCT-ND,DK,https://www.digikey.com/product-detail/en/on-semiconductor/N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
11,"Resistor, 100, 0.25W, 1%, 0805",R_100,R31 R32 R33 R34 R35 R36 R37 R38 R39 R40 R41 R42 R46 R82,R_100,R_0805_OEM,14,https://www.seielect.com/Catalog/SEI-rncp.pdf,RNCP0805FTD100RCT-ND,DK,https://www.digikey.com/products/en?keywords=RNCP0805FTD100RCT-ND
12,"Resistor, 100K, 0.125W, 1%, 0805",R_100K,R49 R50 R51 R53 R54 R55 R57 R58 R59 R65 R66 R67 R69 R70 R71 R73 R74 R75 R76 R77 R78 R79 R80 R81,R_100K,R_0805_OEM,24,https://industrial.panasonic.com/cdbs/www-data/pdf/RDA0000/A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,P100KCCT-ND,DK,https://www.digikey.com/product-detail/en/panasonic-electron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
13,"Resistor, 1K, 0.25W, 1%, 0805",R_1K,R43 R44,R_1K,R_0805_OEM,2,https://www.seielect.com/Catalog/SEI-rncp.pdf,RNCP0805FTD1K00CT-ND,DK,https://www.digikey.com/products/en?keywords=RNCP0805FTD1K00CT-ND
14,RES SMD 3.3 OHM 1% 25W DPAK,R_3.3_25W_TO163,R11 R12 R13 R14 R15 R16 R17 R18 R19 R20,R_3.3_25W_TO163,PWR163,10,https://www.bourns.com/docs/Product-Datasheets/PWR163.pdf,PWR163S-25-3R30F-ND,DK,https://www.digikey.com/products/en?keywords=PWR163S-25-3R30F-ND
15,4.99k resistor,R_4.99K,R21 R22 R23 R24 R25 R26 R27 R28 R29 R30 R45 R47,R_4.99K,R_0805_OEM,12,https://www.digikey.com/product-detail/en/yageo/RC0402FR-074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,RNCP0805FTD4K99CT-ND,DK,https://www.digikey.com/product-detail/en/stackpole-electron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
16,"Resistor, 475, 0.125W, 1%, 0805",R_475,R1 R2 R3 R4 R5 R6 R7 R8 R9 R10,R_475,R_0805_OEM,10,http://www.yageo.com.tw/exep/pages/download/literatures/PYu-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,311-475CRCT-ND,DK,https://www.digikey.com/products/en?keywords=311-475CRCT-ND
17,"Resistor, 60.4, 0.1%, 0.125W, 0805",R_60.4,R48 R52 R56 R60,R_60.4,R_0805_OEM,4,https://industrial.panasonic.com/cdbs/www-data/pdf/RDM0000/A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,P60.4DACT-ND,DK,https://www.digikey.com/product-detail/en/panasonic-electron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
18,Transformer LAN 10/100 base-T,T_LAN_7490100111A,T1,T_LAN_7490100111A,T_LAN_7490100111A,1,https://katalog.we-online.de/pbs/datasheet/7490100111A.pdf,732-5711-1-ND,DK,https://www.digikey.com/product-detail/en/wurth-electronics-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
19,IC EEPROM 1K I2C 400KHZ 8DIP,24AA01,U2,24AA01,SOT-23-5_OEM_24AA01,1,http://ww1.microchip.com/downloads/en/DeviceDoc/21711J.pdf,CAT24AA01TDI-GT3OSCT-ND,DK,https://www.digikey.com/product-detail/en/on-semiconductor/C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
20,Single-Ended 8-Channel/ Differential 4-Channel Analog Multiplexer with SMBus Interface,LTC1380IGN,U5 U6 U7,LTC1380IGN,SSOP-16_3.9x4.9mm_P0.635mm,3,https://www.analog.com/media/en/technical-documentation/data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,LTC1380IGN#PBF-ND,DK,https://www.digikey.com/product-detail/en/linear-technology-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
21,LTC6811-1,LTC6811-1,U1,LTC6811-1,TSSOP-48_LTC6811-1,1,https://www.analog.com/media/en/technical-documentation/data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,LTC6811IG-1-PBF-ND,DK,https://www.digikey.com/product-detail/en/linear-technology-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
22,"Single op-amp, general purpose, -40-+85 C, SC-70-5",MCP6001T-I-LT,U3 U4,MCP6001T-I-LT,SOT-353_SC-70-5,2,http://ww1.microchip.com/downloads/en/DeviceDoc/21733j.pdf,MCP6001T-I/LTCT-ND,DK,https://www.digikey.com/product-detail/en/microchip-technolo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





Component Groups:,22
Component Count:,132
Fitted Components:,132
Number of PCBs:,1
Total components:,132
Schematic Version:,Rev 0
Schematic Date:,2018-10-23
BoM Date:,Wed 27 Mar 2019 12:18:06 AM EDT
Schematic Source:,/home/vscheyer/Desktop/Formula/MKIV-Boards/Boards/BMS_peripheral/BMS_peripheral.sch
KiCad Version:,Eeschema 5.0.2-bee76a0~70~ubuntu16.04.1
